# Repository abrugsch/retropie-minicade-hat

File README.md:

# retropie minicade hat

## Overview

Just a tarted up Raspberry pi GPIO breakout and grouping board aimed at making retropie control panels easier.. no party tricks except for 5v power input.

### PCB layers NOTE:

There are both 4-layer and 2-layer versions of this PCB so in most PCB fabs, you will get merrily rogered for the privilege of those extra 2 layers. There is one fab that doesn't, this is not an advert so I'm not going to say which (unless you ask me) but if you've spent any time having PCB's made, you probably know which one it is. If you want the 2 layer version then go ahead and get the gerbers from the /2-layer folder. If you want to load the 2 layer project into kicad, you still need to get the whole project as it uses the base project schematic as an internal hierarchical schematic sheet.  

### NOTE end

The Retropie minicade (not a) hat is for breaking out groups of pins for Retropie control panels and is pin compatible with the Pimoroni PiCade hat and some of the pin locations are oddly chosen for routing simplicity, nothing else, and there are a few missing features from the Pimoroni board:
  
* No on board I2S DAC.
* No smart switch integrated. Sorry.
* No 'HAT' EEPROM. you'll have to configure the overlays youself. This is why it's not-a-hat.
* No dedicated plasma port (not that hard to wire APA-102's yourself)
* No pimoroni branding (you won't see it once it's all tucked away in your case anyway)  

All this means :

* Smaller. This (not a) hat doesn't cover the CPU area so you can run heat sinks and fans
* Simpler. you're in charge of your own destiny.
* The I2S lines are broken out to use a DAC of your choosing such as a UDA1334 or even an external MAX decoder.
* Chonky 5v in screw terminal for any kind of power supply
* There's still Pi foundation compliant backpower protection
* On-board 3.3v regulator for powering spicy 3.3v peripherals
* H2G2 themed codename (following in the footsteps of my ZZ9 Plural Z Alpha board, this one is Hotblack Desiato - lead singer of the band *DISASTER AREA*)
* Design is in KiCAD 6.0, not nightly so you can open it in the current stable release
* Probably some other things I can't think of right now

## BOM

J1 - 2x20 pin header socket  
J2 - 5mm 2p screw terminal  
J3,4,5,6,7,8 - 2.54mm pitch header pins or sockets, or leave bare for soldering directly. Your choice, I'm not your mum, do what you want.  
C1,C2 - 22uF 0603 6.3v (or better) MLCC capacitor - low ESR  
Q1 - DMG2305UX SOT-23 p-channel FET  
Q2 - MMDT5401 dual PNP transistor SC-70-6  
R1 - 10K 0603  
R2 - 47K 0603  
U1 - AMS1117-3.3 SOT-223-3 (or any other SOT-223-3 fixed 3.3v regulator. whatever you can get from your supplier of choice)

Here are some part numbers from lcsc.com if you are that way inclined. They are from within the JLC PCB assembly stock subset and are 'basic' parts wherever possible if you feel the need to have the factory assemble the boards for you.

C1,C2 = C86295  
J1 = C169819  
Q1 = C150470  
Q2 = C54540  
R1 = C25804  
R2 = C25819  
U1 = C173386 (or a myriad of other LM1117-3.3 clones)  

## Gerbers

Are in the /prod folder for the 4-layer version and /2-Layer/prod folder for the 2-layer version. You probably don't need the 4-layer one, an entire layer for ground is probably overkill for this board, and 2nd signal layer is barely used but it's there if you want it. Have at it. I haven't generated assembly files as it's not hard to hand solder. It's easy enough to generate them yourself if you need to.

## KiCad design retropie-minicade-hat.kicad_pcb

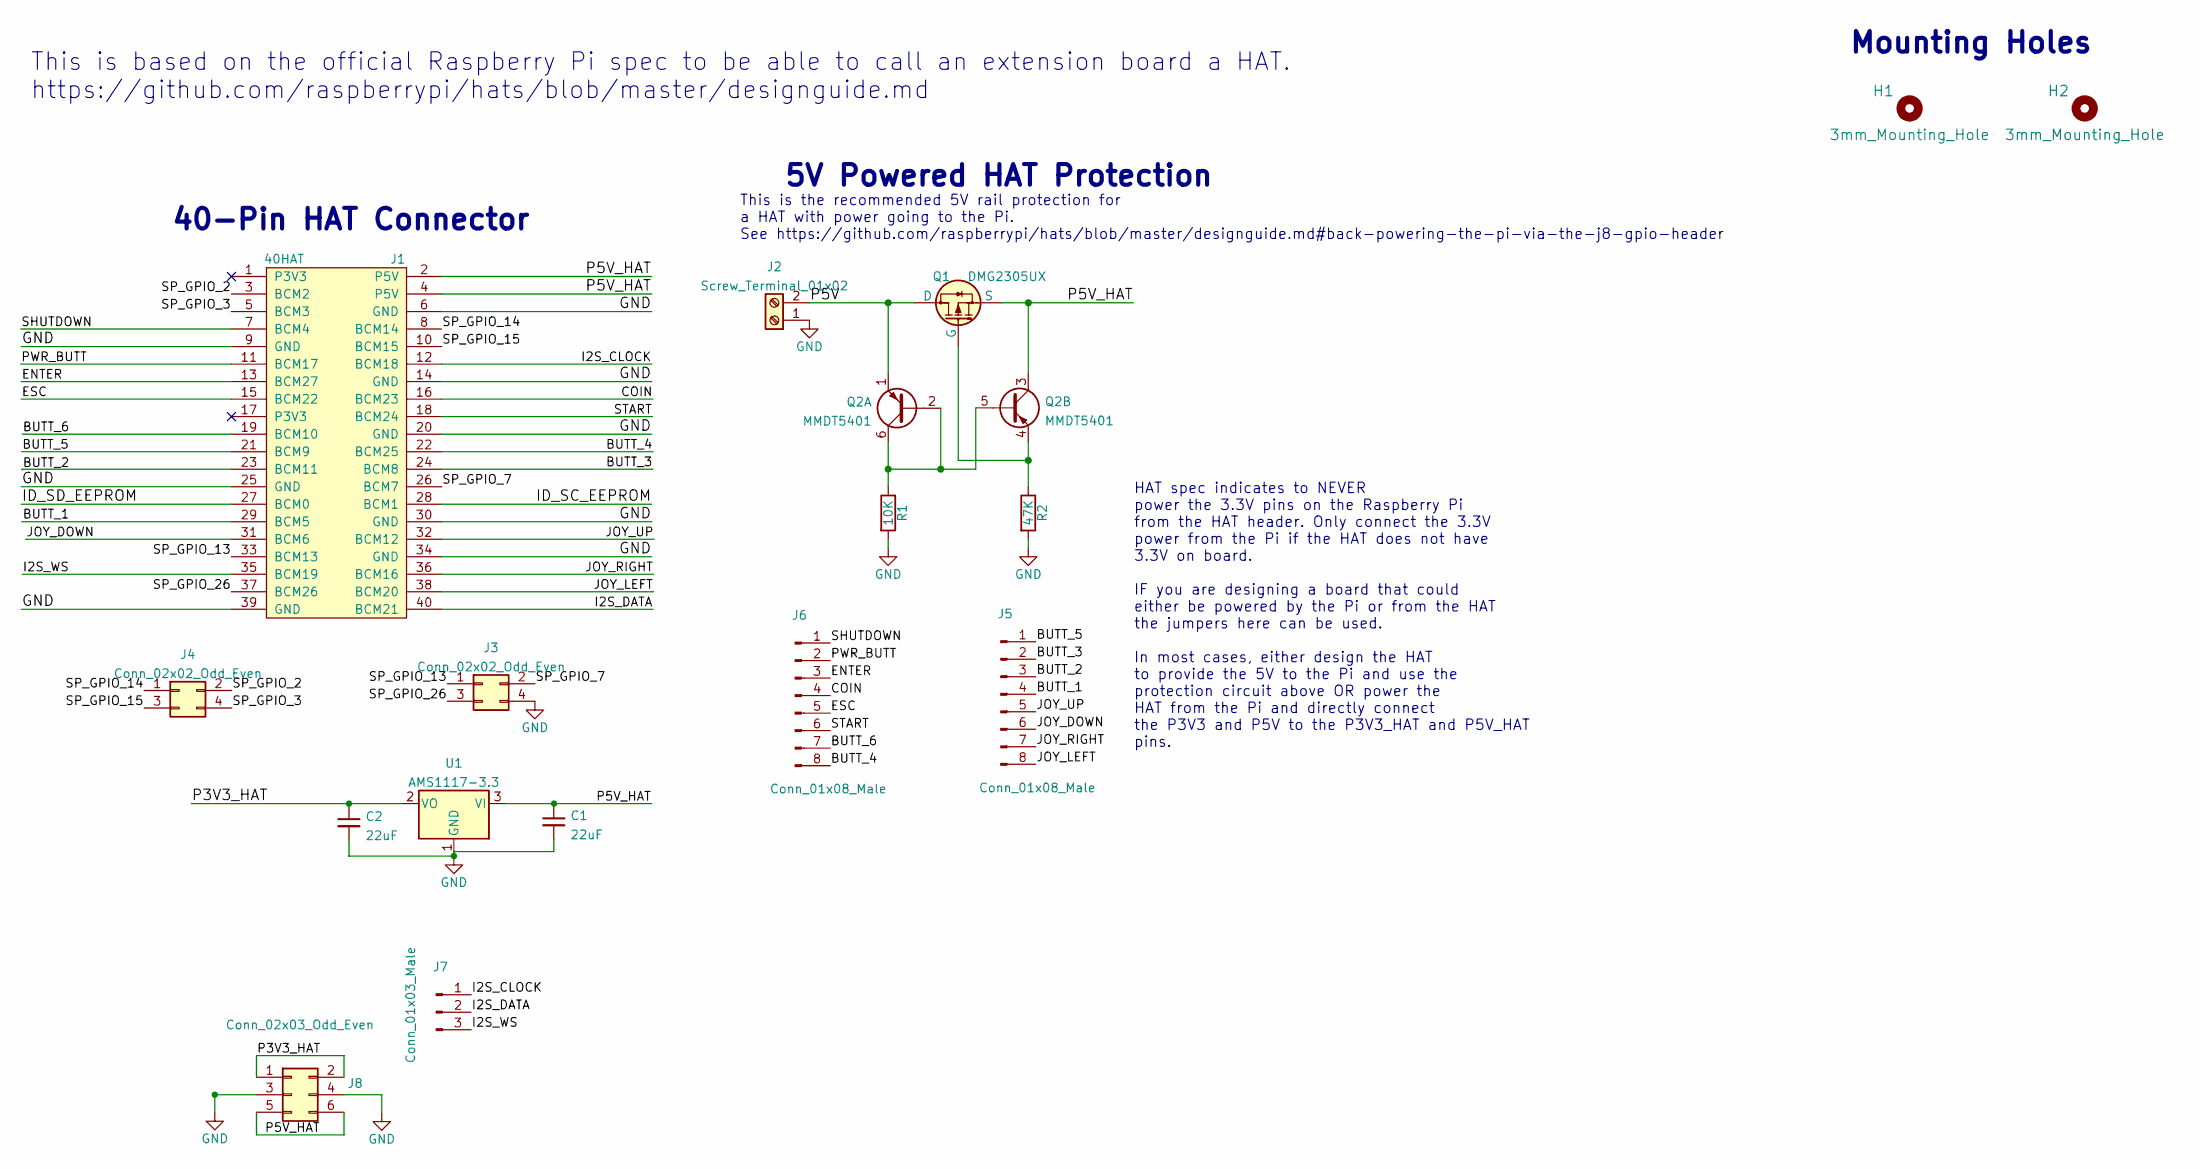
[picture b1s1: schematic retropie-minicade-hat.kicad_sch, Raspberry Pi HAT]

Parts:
C1, C2: 22uF; C_0603_1608Metric; LCSC Part # C59461
H1, H2: 3mm_Mounting_Hole; NPTH_3mm_ID
J1: 40HAT; PinSocket_2x20_P2.54mm_Vertical; LCSC Part # C169819
J2: Screw_Terminal_01x02; TerminalBlock_4Ucon_1x02_P3.50mm_Horizontal; LCSC Part # C8404
J3, J4: Conn_02x02_Odd_Even; PinHeader_2x02_P2.54mm_Vertical
J5, J6: Conn_01x08_Male; PinHeader_1x08_P2.54mm_Vertical
J7: Conn_01x03_Male; PinHeader_1x03_P2.54mm_Vertical
J8: Conn_02x03_Odd_Even; PinHeader_2x03_P2.54mm_Vertical
Q1: DMG2305UX; SOT-23; LCSC Part # C150470
Q2: MMDT5401; SOT-363_SC-70-6; LCSC Part # C54540
R1: 10K; R_0603_1608Metric; LCSC Part # C25804
R2: 47K; R_0603_1608Metric; LCSC Part # C25819
U1: AMS1117-3.3; SOT-223-3_TabPin2; LCSC Part # C6186

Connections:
/BUTT_1: J1.29 (BCM5), J5.4
/BUTT_2: J1.23 (BCM11), J5.3
/BUTT_3: J1.24 (BCM8), J5.2
/BUTT_4: J1.22 (BCM25), J6.8
/BUTT_5: J1.21 (BCM9), J5.1
/BUTT_6: J1.19 (BCM10), J6.7
/COIN: J1.16 (BCM23), J6.4
/ENTER: J1.13 (BCM27), J6.3
/ESC: J1.15 (BCM22), J6.5
/I2S_CLOCK: J1.12 (BCM18), J7.1
/I2S_DATA: J1.40 (BCM21), J7.2
/I2S_WS: J1.35 (BCM19), J7.3
/ID_SC_EEPROM: J1.28 (BCM1)
/ID_SD_EEPROM: J1.27 (BCM0)
/JOY_DOWN: J1.31 (BCM6), J5.6
/JOY_LEFT: J1.38 (BCM20), J5.8
/JOY_RIGHT: J1.36 (BCM16), J5.7
/JOY_UP: J1.32 (BCM12), J5.5
/P3V3_HAT: C2.1, J8.1, J8.2, U1.2 (VO)
/P5V: J2.2, Q1.3 (D), Q2.1 (E1)
/P5V_HAT: C1.1, J1.2 (P5V), J1.4 (P5V), J8.5, J8.6, Q1.2 (S), Q2.3 (C2), U1.3 (VI)
/PWR_BUTT: J1.11 (BCM17), J6.2
/SHUTDOWN: J1.7 (BCM4), J6.1
/SP_GPIO_2: J1.3 (BCM2), J4.2
/SP_GPIO_3: J1.5 (BCM3), J4.4
/SP_GPIO_7: J1.26 (BCM7), J3.2
/SP_GPIO_13: J1.33 (BCM13), J3.1
/SP_GPIO_14: J1.8 (BCM14), J4.1
/SP_GPIO_15: J1.10 (BCM15), J4.3
/SP_GPIO_26: J1.37 (BCM26), J3.3
/START: J1.18 (BCM24), J6.6
GND: C1.2, C2.2, J1.6 (GND), J1.9 (GND), J1.14 (GND), J1.20 (GND), J1.25 (GND), J1.30 (GND), J1.34 (GND), J1.39 (GND), J2.1, J3.4, J8.3, J8.4, R1.2, R2.2, U1.1 (GND)
unnamed: Q1.1 (G), Q2.4 (E2), R2.1
unnamed: Q2.2 (B1), Q2.5 (B2), Q2.6 (C1), R1.1

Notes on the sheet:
This is based on the official Raspberry Pi spec to be able to call an extension board a HAT. https://github.com/raspberrypi/hats/blob/master/designguide.md
This is the recommended 5V rail protection for a HAT with power going to the Pi. See https://github.com/raspberrypi/hats/blob/master/designguide.md#back-powering-the-pi-via-the-j8-gpio-header
5V Powered HAT Protection
HAT spec indicates to NEVER power the 3.3V pins on the Raspberry Pi from the HAT header. Only connect the 3.3V power from the Pi if the HAT does not have 3.3V on board. IF you are designing a board that could either be powered by the Pi or from the HAT the jumpers here can be used. In most cases, e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
40-Pin HAT Connector
Mounting Holes

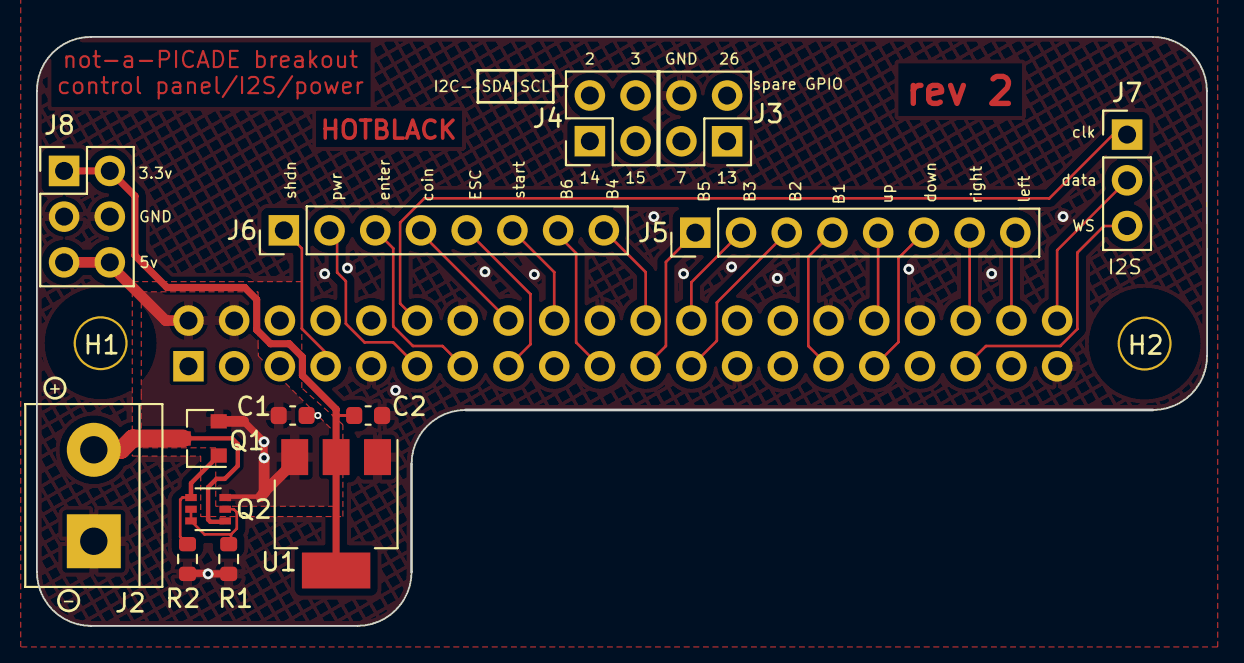
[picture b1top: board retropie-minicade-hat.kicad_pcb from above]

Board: 4 copper layers, 65.0 x 32.7 mm, 17 parts (1 on the bottom side), 32 nets.

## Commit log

2022-12-01 updated readme
    and added board pics
2022-12-01 Update of README
2022-12-02 change to C1 and C2 values
    update to 22uF from 10uF in BOM.
    No change to production files
2022-12-05 Update BOM with component numbers. ignore auto backups
2022-12-05 added files to ignore list
2022-12-05 changed the H2G2 quote to something related to Hotblack
2022-12-05 proper MD line endings on readme
2022-12-05 updated gerbers after text changes
2022-12-05 tweaks to pin order to rationalize trace routes
2022-12-05 update images to new revision
2022-12-08 Delete minicade-hat-0.5.zip
    removing as the silkscreen labels for the button pins are wrong after a layout/routing tweak
2022-12-09 re-did the silkscreen labels
    pins and traces were changed but not the pin labels. fixed
2022-12-09 saved silkscreen changes
2022-12-09 Added 2-layer version of the PCB
    forked the main project to spin a 2-layer version
2022-12-09 missed prom previous commit
2025-02-17 updated images and gerbers (Rev2)
    updated gerbers to latest version of PCB
